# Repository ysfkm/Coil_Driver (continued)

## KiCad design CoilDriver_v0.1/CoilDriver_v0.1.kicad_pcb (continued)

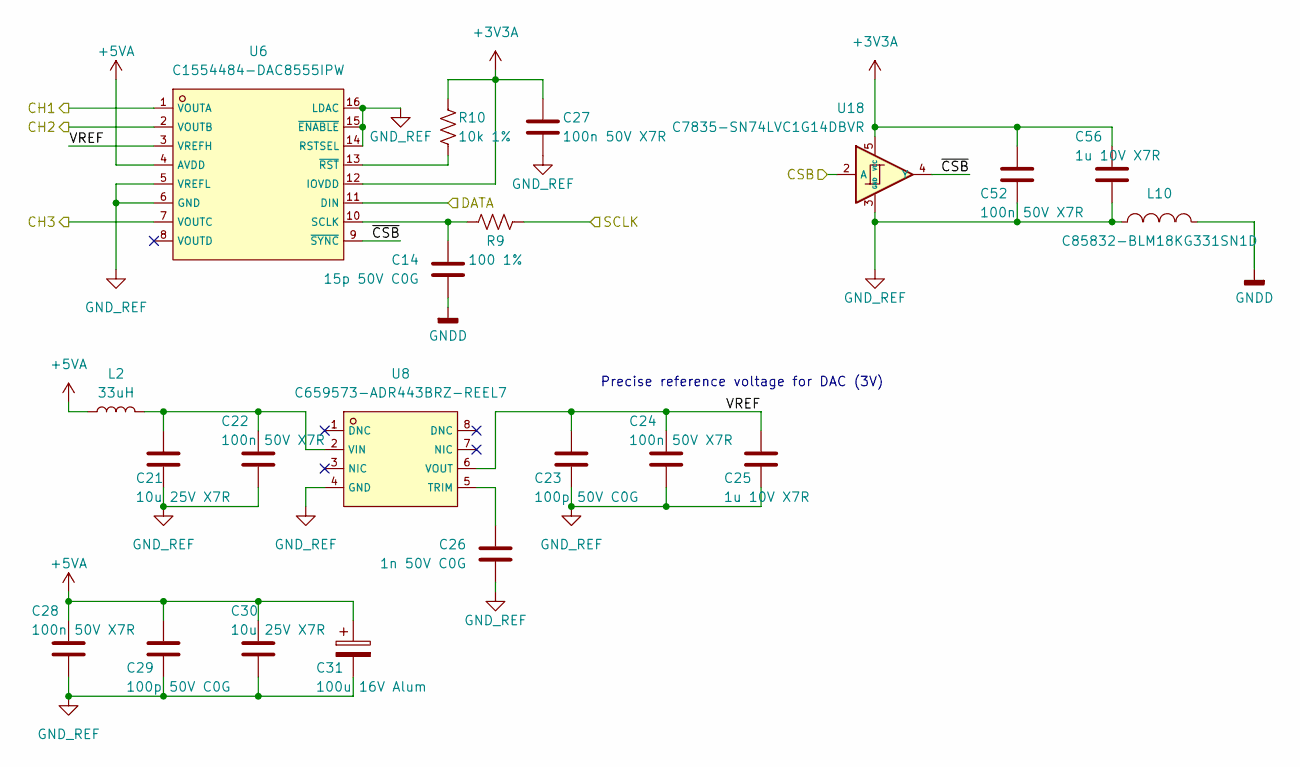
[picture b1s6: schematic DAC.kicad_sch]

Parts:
C14: 15p 50V C0G; C_0402_1005Metric; LCSC C880657
C21, C30: 10u 25V X7R; C_0805_2012Metric; LCSC C3039694
C22, C24, C27, C28, C52: 100n 50V X7R; C_0402_1005Metric; LCSC C307331
C23, C29: 100p 50V C0G; C_0402_1005Metric; LCSC C1546
C25, C56: 1u 10V X7R; C_0402_1005Metric; LCSC C7500381
C26: 1n 50V C0G; C_0402_1005Metric; LCSC C307441
C31: 100u 16V Alum; C37308-CAP-SMD_BD6.3-L6.6-W6.6-LS7.2-FD; LCSC C37308
L2: 33uH; L_0603_1608Metric; LCSC C5339211
L10: C85832-BLM18KG331SN1D; C85832-L0603; LCSC C85832
R9: 100 1%; R_0402_1005Metric; LCSC C25076
R10: 10k 1%; R_0402_1005Metric; LCSC C2906861
U6: C1554484-DAC8555IPW; C1554484-TSSOP-16_L5.0-W4.4-P0.65-LS6.4-TL; LCSC C1554484
U8: C659573-ADR443BRZ-REEL7; C659573-SOIC-8_L4.9-W3.9-P1.27-LS6.0-BL; LCSC C659573
U18: C7835-SN74LVC1G14DBVR; C7835-SOT-23-5_L3.0-W1.7-P0.95-LS2.8-BR; LCSC C7835

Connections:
+3V3A: C27.1, C52.1, C56.1, R10.1, U6.12 (IOVDD), U18.5 (VCC); also elsewhere on the board
+5VA: C28.1, C29.1, C30.1, C31.1, L2.1, U6.4 (AVDD); also elsewhere on the board
/CSB: U18.2 (A); also elsewhere on the board
/DAC1: U6.1 (VOUTA); also elsewhere on the board
/DAC2: U6.2 (VOUTB); also elsewhere on the board
/DAC3: U6.7 (VOUTC); also elsewhere on the board
/DAC/VREF: C23.1, C24.1, C25.1, U6.3 (VREFH), U8.6 (VOUT)
/DAC/~CSB: U6.9 (~SYNC), U18.4 (Y)
/SCLK: R9.2; also elsewhere on the board
/SDIO_0: U6.11 (DIN); also elsewhere on the board
GNDD: C14.2, L10.2; also elsewhere on the board
GND_REF: C21.2, C22.2, C23.2, C24.2, C25.2, C26.2, C27.2, C28.2, C29.2, C30.2, C31.2, C52.2, C56.2, L10.1, U6.5 (VREFL), U6.6 (GND), U6.14 (RSTSEL), U6.15 (~ENABLE), U6.16 (LDAC), U8.4 (GND), U18.3 (GND); also elsewhere on the board
unnamed: C14.1, R9.1, U6.10 (SCLK)
unnamed: R10.2, U6.13 (~RST)
unnamed: C26.1, U8.5 (TRIM)
unnamed: C21.1, C22.1, L2.2, U8.2 (VIN)

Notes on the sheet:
Precise reference voltage for DAC (3V)

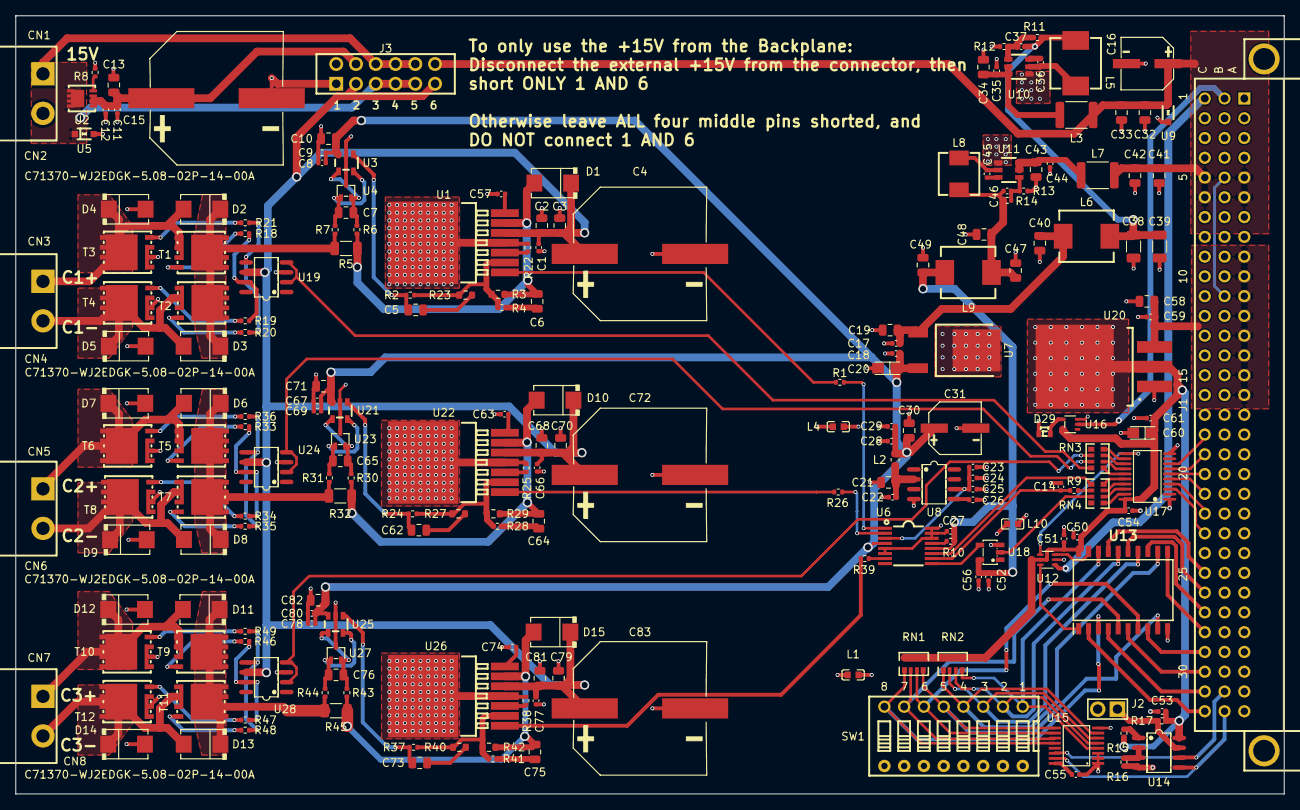
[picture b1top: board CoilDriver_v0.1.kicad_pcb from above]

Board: 4 copper layers, 163.0 x 100.0 mm, 214 parts (0 on the bottom side), 139 nets.

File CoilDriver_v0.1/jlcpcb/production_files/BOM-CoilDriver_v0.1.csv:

Comment,Designator,Footprint,LCSC,Quantity
C113280 - SN74LVC573APWR,U17,C113280-TSSOP-20_L6.5-W4.4-P0.65-LS6.4-BL,C113280,1
C114502 - M24C02-FDW,U14,C114502-SOIC-8_L4.9-W3.9-P1.27-LS6.0-BL,C114502,1
10u 16V Tant,"C20,C60",C119051-CASE-A_3216,C119051,2
10 1%,"R30,R31,R43,R44,R6,R7",R_0402_1005Metric,C138066,6
10n 50V X7R,"C57,C63,C74",C_0402_1005Metric,C15195,3
100p 50V C0G,"C11,C23,C29,C37,C46,C67,C78,C8",C_0402_1005Metric,C1546,8
C1554484-DAC8555IPW,U6,C1554484-TSSOP-16_L5.0-W4.4-P0.65-LS6.4-TL,C1554484,1
C157411-LD29150DT50R,U7,C157411-TO-252-3_L6.5-W5.8-P4.58-BL,C157411,1
6.8uH,L8,C177249-IND-SMD_L5.4-W5.2_FXL0530,C177249,1
C1855802-INA293B2IDBVR,"U21,U25,U3",C1855802-SOT-23-5_L2.9-W1.6-P0.95-LS2.8-BR,C1855802,3
C2071868-AP63200WU-7,"U10,U11",C2071868-SOT-23-6_L2.9-W1.6-P0.95-LS2.8-BR,C2071868,2
C207245-SD15C-01FTG,U5,C207245-SOD-323_L1.7-W1.3-LS2.5-BI-1,C207245,1
22n C0G,"C6,C64,C75",C_0805_2012Metric,C2181592,3
C22461594 - PCF8574AP,U15,C22461594-TSSOP-16_L5.0-W4.4-P0.65-LS6.4-BL-1,C22461594,1
22uH >0.5A,"L3,L7",L_1812_4532Metric,C22469096,2
C22469958 - 74LVC1GU04,U16,C22469958-SOT-353-5_L2.1-W1.3-P0.65-LS2.3-BL,C22469958,1
100 1%,R9,R_0402_1005Metric,C25076,1
R33_Pack,"RN3,RN4",C25508-RES-ARRAY-SMD_0603-8P-L3.2-W1.6-BL,C25508,2
C259972-LM1084S-3.3_TR,U20,C259972-TO-263-3_L8.6-W10.2-P2.54-LS14.4-TL,C259972,1
C2653336-74FCT521CTSOG8,U13,C2653336-SOIC127P1032X265-20N,C2653336,1
C2687965-OPA548FKTWT,"U1,U22,U26",C2687965-TO-263-7_L10.2-W8.9-P1.27-LS15.2-BL,C2687965,3
100u 35V Alum,C16,C2887272-CAP-SMD_BD6.3-L6.6-W6.6-LS7.2-FD_3,C2887272,1
10k 1%,"R1,R10,R15,R16,R17,R2,R24,R26,R37,R39,R8",R_0402_1005Metric,C2906861,11
1k 5%,"R18,R19,R20,R21,R33,R34,R35,R36,R46,R47,R48,R49",R_0402_1005Metric,C2906899,12
30k 1%,R12,R_0402_1005Metric,C2909347,1
62k 1%,R13,R_0402_1005Metric,C2909375,1
C29718-R10k_Pack04,"RN1,RN2",C29718-RES-ARRAY-SMD_0603-8P-L3.2-W1.6-BL,C29718,2
196k 1%,"R11,R14",R_0402_1005Metric,C3013157,2
453k 1%,"R28,R4,R41",R_0402_1005Metric,C3013172,3
10u 25V X7R,"C10,C13,C19,C2,C21,C3,C30,C32,C33,C34,C40,C41,C42,C43,C49,C58,C68,C70,C71,C79,C81,C82",C_0805_2012Metric,C3039694,22
C306220-826925-6,J3,C306220-CONN-TH_12P-P2.54_826925-6,C306220,1
100n 50V X7R,"C1,C12,C17,C18,C22,C24,C27,C28,C35,C36,C44,C45,C50,C51,C52,C54,C59,C61,C66,C69,C77,C80,C9",C_0402_1005Metric,C307331,23
1n 50V C0G,C26,C_0402_1005Metric,C307441,1
4k02 1%,"R22,R25,R38",R_0402_1005Metric,C324800,3
C3697-WJ2EDGRC-5.08-02P-14-00A,"CN1,CN3,CN5,CN7",C3697-CONN-TH_2P-P5.08_WJ2EDGRC-5.08-2P,C3697,4
100u 16V Alum,C31,C37308-CAP-SMD_BD6.3-L6.6-W6.6-LS7.2-FD,C37308,1
2200u 35V Alum,"C15,C4,C72,C83",C3829879-CAP-SMD_BD16.0-L17.0-W17.0-LS18.0-FD,C3829879,4
C458084-DS-08RP,SW1,C458084-SW-TH_DS-08RP,C458084,1
Conn_01x02,J2,C492401-HDR-TH_2P-P2.54-V-M,C492401,1
C506609-SISS27DN-T1-GE3,U2,C506609-POWERPAK-1212-8_L3.3-W3.3-P0.65-BL-EP,C506609,1
C50793 - NC7WZ14P6X,U12,C50793-SC-70-6_L2.2-W1.3-P0.65-LS2.2-BR,C50793,1
C511854-SS54SMB,"D1,D10,D11,D12,D13,D14,D15,D2,D3,D4,D5,D6,D7,D8,D9",C511854-SMB_L4.6-W3.6-LS5.3-RD,C511854,15
C5173361-DIN41612-CONN-TH_96P,J1,C5173361-DIN41612-96P,C5173361,1
33uH,L2,L_0603_1608Metric,C5339211,1
10uH,L5,C540965-IND-SMD_L6.5-W6.5_VISHAY,C540965,1
"C550069-BZB784-C15,115","U23,U27,U4",C550069-SOT-323-3_L2.0-W1.3-P1.30-LS2.1-BR,C550069,3
C637542-MIC4428YM,"U19,U24,U28",C637542-SOIC-8_L4.9-W3.9-P1.27-LS6.0-BL,C637542,3
C659573-ADR443BRZ-REEL7,U8,C659573-SOIC-8_L4.9-W3.9-P1.27-LS6.0-BL,C659573,1
C71370-WJ2EDGK-5.08-02P-14-00A,"CN2,CN4,CN6,CN8",C71370-FL_001,C71370,4
C7220836-BSC010N04LS6ATMA1,"T1,T10,T11,T12,T2,T3,T4,T5,T6,T7,T8,T9",C7220836-TDSON-8_L6.0-W5.0-P1.27-LS6.2-BL_1,C7220836,12
3.3u 25V X7R,"C65,C7,C76",C_0805_2012Metric,C7393948,3
0.02 1W 1%,"R32,R45,R5",R_1206_3216Metric,C7420010,3
22u 16V X7R,"C38,C39",C_1206_3216Metric,C7472972,2
1u 10V X7R,"C25,C53,C55,C56",C_0402_1005Metric,C7500381,4
C7835-SN74LVC1G14DBVR,U18,C7835-SOT-23-5_L3.0-W1.7-P0.95-LS2.8-BR,C7835,1
22uH,"L6,L9",C842901-IND-SMD_L7.0-W6.6,C842901,2
C85832-BLM18KG331SN1D,"L1,L10,L4",C85832-L0603,C85832,3
15p 50V C0G,C14,C_0402_1005Metric,C880657,1
C907854-SD12C,U9,C907854-SOD-323_L1.7-W1.3-LS2.5-BI,C907854,1
22u 10V X7R,"C47,C48",C_0805_2012Metric,C907991,2
C965863-XL-1606UGC,D29,C965863-LED-SMD_L1.7-W1.1-R-RD_ORANGE,C965863,1
